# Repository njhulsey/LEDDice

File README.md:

# LEDDice
During my senior year of highschool I designed a circuit board for a teacher to use in his engineering class. This was meant to help teach
kids about soldering and electronics. On the board there is a button, Attiny45, and 7 LEDS. When the button is pressed, the leds will roll and simulate a dice. 

WHAT I LEARNED:
- ATTINY 45 programming
- Circuit Design
- Soldering

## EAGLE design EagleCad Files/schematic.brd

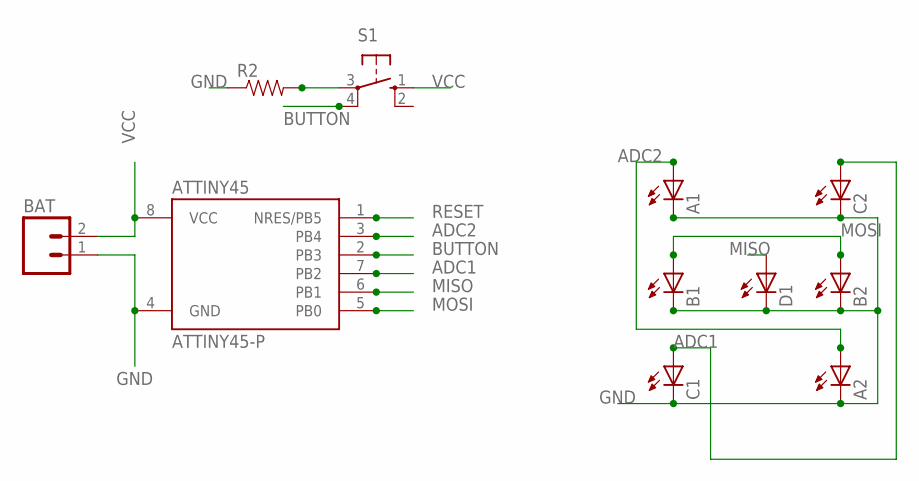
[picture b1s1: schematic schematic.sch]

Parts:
A1, A2: LED5MM
ATTINY45: ATTINY45-P; PDIP08_300MIL
B1, B2: LED5MM
BAT: M02PTH; 1X02
C1, C2: LED5MM
D1: LED5MM
R2: 10KOHM-1/6W-5%(PTH)KIT; AXIAL-0.3-KIT
S1: 40-XX; B3F-40XX

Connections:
ADC1: ATTINY45.7 (PB2), C1.A, C2.A
ADC2: A1.A, A2.A, ATTINY45.3 (PB4)
BUTTON: ATTINY45.2 (PB3), S1.4 (P1)
GND: A1.K (C), A2.K (C), ATTINY45.4 (GND), B1.K (C), B2.K (C), BAT.1, C1.K (C), C2.K (C), D1.K (C), R2.P$1 (1)
MISO: ATTINY45.6 (PB1), D1.A
MOSI: ATTINY45.5 (PB0), B1.A, B2.A
unnamed: R2.P$2 (2), S1.3
RESET: ATTINY45.1 (NRES/PB5)
VCC: ATTINY45.8 (VCC), BAT.2, S1.1 (S)

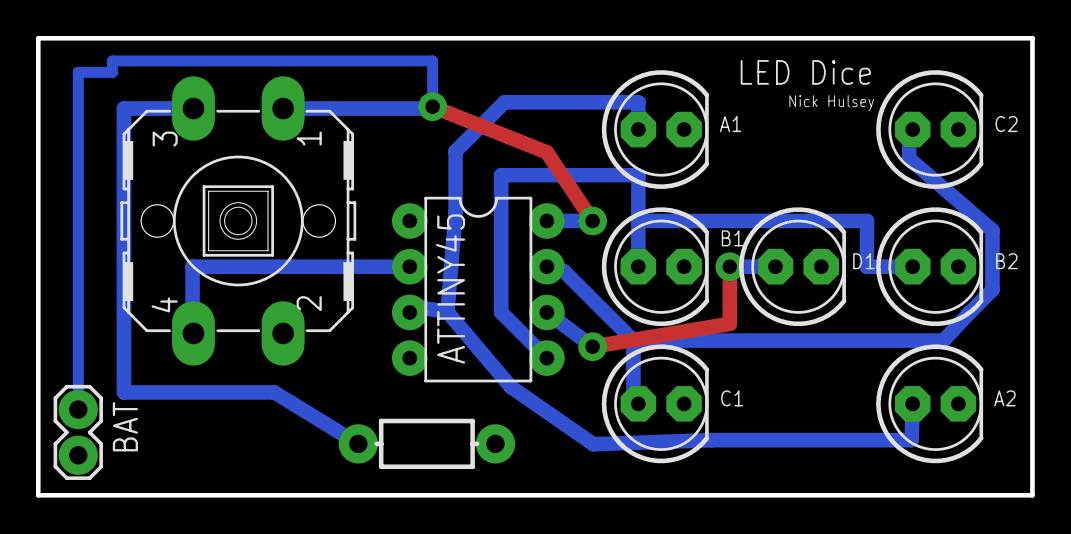
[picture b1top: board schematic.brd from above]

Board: 2 copper layers, 55.2 x 25.4 mm, 11 parts (0 on the bottom side), 8 nets.

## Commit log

2018-03-11 Create init

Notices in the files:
parts and their libraries:
SparkFun-Resistors: Licensing: Creative Commons ShareAlike 4.0 International - https://creativecommons.org/licenses/by-sa/4.0
